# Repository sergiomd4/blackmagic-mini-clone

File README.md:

Black Magic Mini Clone
========================================

Black Magic Mini is a reduced version of the Black Magic board in terms of number of components.

It is an easy-to-use board used for debugging embedded microcontrollers. It supports several targets from manufacturers such as STMicroelectronics, Atmel, Nordic Semiconductor, NXP, Texas Instruments, Freescale, Silicon Labs, Xilinx or Raspberry Pi.

GNU debugger
-------------------
The Black Magic GNU DeBugger (GDB) server features:
* Automatic target detection
* No need for target specific configuration scripts
* Easily scriptable
* Interface to the host computer does not require special drivers
* Full debugging functionality
* Works with Windows, Linux and Mac environments

Repository Contents
-------------------

* **/Production** - Gerber files, drill files, BOM, CPL file
* **/Hardware** - KiCad PCB files, footprints library
* **/Documents** - Schematics pdf

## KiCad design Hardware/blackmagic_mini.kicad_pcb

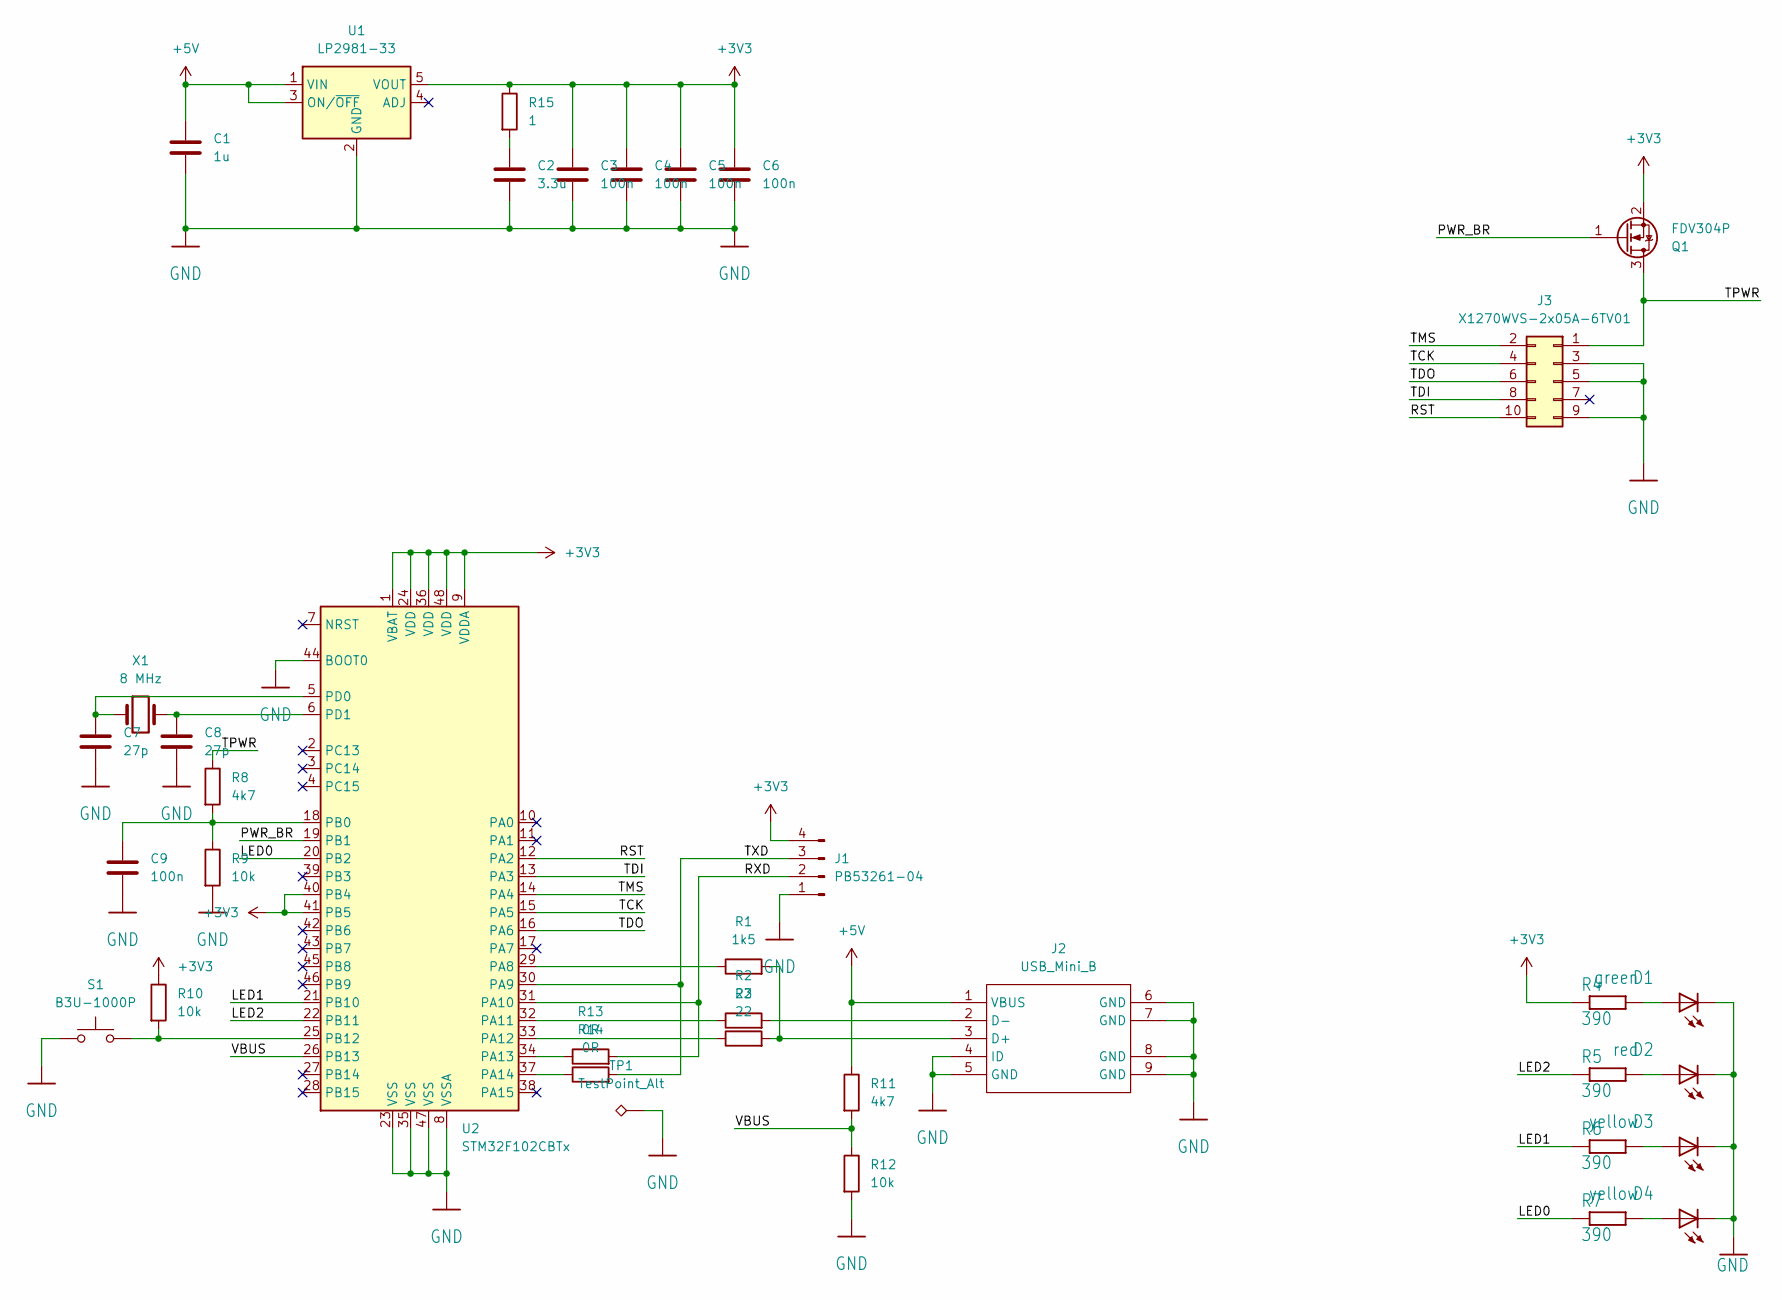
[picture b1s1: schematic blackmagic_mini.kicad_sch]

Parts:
C1: 1u; C_0402_1005Metric; LCSC Number Part C107372
C2: 3.3u; C_0603_1608Metric; LCSC Number Part C51412
C3, C4, C5, C6, C9: 100n; C_0402_1005Metric; LCSC Number Part C60474
C7, C8: 27p; C_0402_1005Metric; LCSC Number Part C1557
D1: green; LED_0603_1608Metric; LCSC Number Part C434420
D2: red; LED_0603_1608Metric; LCSC Number Part C375444
D3, D4: yellow; LED_0603_1608Metric; LCSC Number Part C89811
J1: PB53261−04; X1311WVS-04J-C18D42R1; LCSC Number Part C2881571
J2: USB_Mini_B; U-M-M5SS-W-2; LCSC Number Part C91144
J3: X1270WVS-2x05A-6TV01; LCSC Number Part C2962222
Q1: FDV304P; SOT-23; LCSC Number Part C709971
R1: 1k5; R_0402_1005Metric; LCSC Number Part C25867
R2, R3: 22; R_0402_1005Metric; LCSC Number Part C25092
R4, R5, R6, R7: 390; R_0402_1005Metric; LCSC Number Part C25163
R8, R11: 4k7; R_0402_1005Metric; LCSC Number Part C304616
R9, R10, R12: 10k; R_0402_1005Metric; LCSC Number Part C140214
R13, R14: 0R; R_0402_1005Metric; LCSC Number Part C106231
R15: 1; R_0402_1005Metric; LCSC Number Part C25147
S1: B3U-1000P; LCSC Number Part C231329
TP1: TestPoint_Alt; TestPoint_Pad_1.0x1.0mm
U1: LP2981-33; SOT-23-5; LCSC Number Part C129997
U2: STM32F102CBTx; LQFP-48_7x7mm_P0.5mm; LCSC Number Part C8304
X1: 8 MHz; G5308000201080; LCSC Number Part C390781

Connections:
+3V3: C3.1, C4.1, C5.1, C6.1, J1.4, Q1.2 (S), R4.1, R10.1, R15.1, U1.5 (VOUT), U2.1 (VBAT), U2.9 (VDDA), U2.24 (VDD), U2.36 (VDD), U2.40 (PB4), U2.41 (PB5), U2.48 (VDD)
+5V: C1.1, J2.1 (VBUS), R11.1, U1.1 (VIN), U1.3 (ON/~OFF)
/LED0: R7.1, U2.20 (PB2)
/LED1: R6.1, U2.21 (PB10)
/LED2: R5.1, U2.22 (PB11)
/PWR_BR: Q1.1 (G), U2.19 (PB1)
/RST: J3.10, U2.12 (PA2)
/RXD: J1.2, R13.2, U2.31 (PA10)
/TCK: J3.4, U2.15 (PA5)
/TDI: J3.8, U2.13 (PA3)
/TDO: J3.6, U2.16 (PA6)
/TMS: J3.2, U2.14 (PA4)
/TPWR: J3.1, Q1.3 (D), R8.1
/TXD: J1.3, R14.2, U2.30 (PA9)
/VBUS: R11.2, R12.1, U2.26 (PB13)
GND: C1.2, C2.2, C3.2, C4.2, C5.2, C6.2, C7.2, C8.2, C9.2, D1.2 (C), D2.2 (C), D3.2 (C), D4.2 (C), J1.1, J2.4 (ID), J2.5 (GND), J2.6 (GND), J2.7 (GND), J2.8 (GND), J2.9 (GND), J3.3, J3.5, J3.9, R9.2, R12.2, S1.1, TP1.1, U1.2 (GND), U2.8 (VSSA), U2.23 (VSS), U2.35 (VSS), U2.44 (BOOT0), U2.47 (VSS)
unnamed: D1.1 (A), R4.2
unnamed: D2.1 (A), R5.2
unnamed: D3.1 (A), R6.2
unnamed: D4.1 (A), R7.2
unnamed: J2.2 (D-), R2.2
unnamed: J2.3 (D+), R1.2, R3.2
unnamed: C9.1, R8.2, R9.1, U2.18 (PB0)
unnamed: R10.2, S1.2, U2.25 (PB12)
unnamed: C2.1, R15.2
unnamed: R1.1, U2.29 (PA8)
unnamed: R2.1, U2.32 (PA11)
unnamed: R3.1, U2.33 (PA12)
unnamed: R13.1, U2.34 (PA13)
unnamed: R14.1, U2.37 (PA14)
unnamed: C7.1, U2.5 (PD0), X1.1
unnamed: C8.1, U2.6 (PD1), X1.2

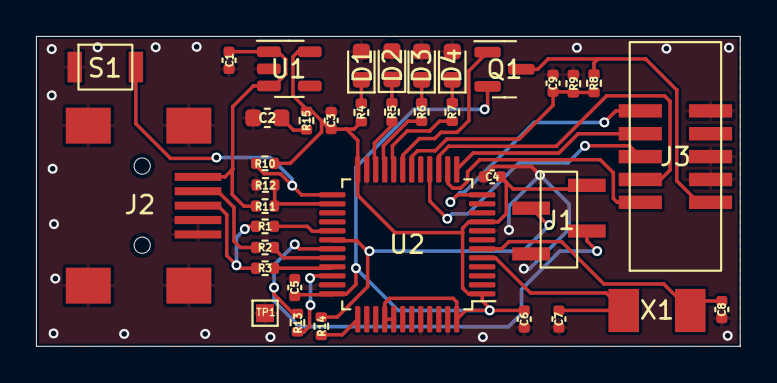
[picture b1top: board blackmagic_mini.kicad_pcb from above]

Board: 2 copper layers, 39.1 x 17.2 mm, 37 parts (0 on the bottom side), 32 nets.

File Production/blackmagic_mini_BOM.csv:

"Source:","C:\Users\Sergio\Documents\EOS\blackmagic-hardware-master\blackmagic_mini_KiCAD\blackmagic_mini.kicad_sch"
"Date:","05/09/2022 13:16:44"
"Tool:","Eeschema (6.0.7)"
"Generator:","C:\Program Files\KiCad\6.0\bin\scripting\plugins/bom_csv_grouped_by_value.py"
"Component Count:","36"

"Individual Components:"

"Item","Qty","Reference(s)","Value","LibPart","Footprint","Datasheet","LCSC Number Part"
"","","C1","1u","Device:C","Capacitor_SMD:C_0402_1005Metric","~","C107372"
"","","C2","3.3u","Device:C","Capacitor_SMD:C_0603_1608Metric","~","C51412"
"","","C3","100n","Device:C","Capacitor_SMD:C_0402_1005Metric","~","C60474"
"","","C4","100n","Device:C","Capacitor_SMD:C_0402_1005Metric","~","C60474"
"","","C5","100n","Device:C","Capacitor_SMD:C_0402_1005Metric","~","C60474"
"","","C6","100n","Device:C","Capacitor_SMD:C_0402_1005Metric","~","C60474"
"","","C7","27p","Device:C","Capacitor_SMD:C_0402_1005Metric","~","C1557"
"","","C8","27p","Device:C","Capacitor_SMD:C_0402_1005Metric","~","C1557"
"","","C9","100n","Device:C","Capacitor_SMD:C_0402_1005Metric","~","C60474"
"","","D1","green",":LEDCHIPLED_0603_1","LED_SMD:LED_0603_1608Metric","","C434420"
"","","D2","red",":LEDCHIPLED_0603_2","LED_SMD:LED_0603_1608Metric","","C375444"
"","","D3","yellow",":LEDCHIPLED_0603_3","LED_SMD:LED_0603_1608Metric","","C89811"
"","","D4","yellow","bmp_entropia-eagle-import:LEDCHIPLED_0603","LED_SMD:LED_0603_1608Metric","","C89811"
"","","J1","PB53261−04","Connector:Conn_01x04_Male","EOS:X1311WVS-04J-C18D42R1","~","C2881571"
"","","J2","USB_Mini_B",":USB_Mini_B_1","EOS:U-M-M5SS-W-2","","C91144"
"","","J3","X1270WVS-2x05A-6TV01","Connector_Generic:Conn_02x05_Odd_Even","EOS:X1270WVS-2x05A-6TV01","~","C2962222"
"","","Q1","FDV304P","Transistor_FET:2N7000","Package_TO_SOT_SMD:SOT-23","https://www.vishay.com/docs/70226/70226.pdf","C709971"
"","","R1","1k5","Device:R","Resistor_SMD:R_0402_1005Metric","~","C25867"
"","","R2","22","Device:R","Resistor_SMD:R_0402_1005Metric","~","C25092"
"","","R3","22","Device:R","Resistor_SMD:R_0402_1005Metric","~","C25092"
"","","R4","390","bmp_entropia-eagle-import:R-EU_R0603","Resistor_SMD:R_0402_1005Metric","","C25163"
"","","R5","390","bmp_entropia-eagle-import:R-EU_R0603","Resistor_SMD:R_0402_1005Metric","","C25163"
"","","R6","390","bmp_entropia-eagle-import:R-EU_R0603","Resistor_SMD:R_0402_1005Metric","","C25163"
"","","R7","390","bmp_entropia-eagle-import:R-EU_R0603","Resistor_SMD:R_0402_1005Metric","","C25163"
"","","R8","4k7","Device:R","Resistor_SMD:R_0402_1005Metric","~","C304616"
"","","R9","10k","Device:R","Resistor_SMD:R_0402_1005Metric","~","C140214"
"","","R10","10k","Device:R","Resistor_SMD:R_0402_1005Metric","~","C140214"
"","","R11","4k7","Device:R","Resistor_SMD:R_0402_1005Metric","~","C304616"
"","","R12","10k","Device:R","Resistor_SMD:R_0402_1005Metric","~","C140214"
"","","R13","0R","Device:R","Resistor_SMD:R_0402_1005Metric","~","C106231"
"","","R14","0R","Device:R","Resistor_SMD:R_0402_1005Metric","~","C106231"
"","","R15","1","Device:R","Resistor_SMD:R_0402_1005Metric","~","C25147"
"","","S1","B3U-1000P","Switch:SW_Push","EOS:B3U-1000P","~","C231329"
"","","U1","LP2981-33","Regulator_Linear:LP2980-ADJ","Package_TO_SOT_SMD:SOT-23-5","http://www.ti.com/lit/ds/symlink/lp2980-adj.pdf","C129997"
"","","U2","STM32F102CBTx","MCU_ST_STM32F1:STM32F102CBTx","Package_QFP:LQFP-48_7x7mm_P0.5mm","http://www.st.com/st-web-ui/static/active/en/resource/techni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","C8304"
"","","X1","8 MHz","Device:Crystal","EOS:G5308000201080","~","C390781"

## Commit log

2022-09-13 Update gitignore
2022-09-13 Add schematics
2022-09-13 Add images
2022-09-13 Add BOM
2022-09-13 Add Drill Files
2022-09-13 Add CPL file
2022-09-13 Add Gerber Files
2022-09-13 Add KiCad files
2022-09-13 Add footprints library
